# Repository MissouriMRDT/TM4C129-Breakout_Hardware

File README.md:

# TM4C129-Breakout_Hardware
A Hardware breakout for the TM4C129 Microcontroller

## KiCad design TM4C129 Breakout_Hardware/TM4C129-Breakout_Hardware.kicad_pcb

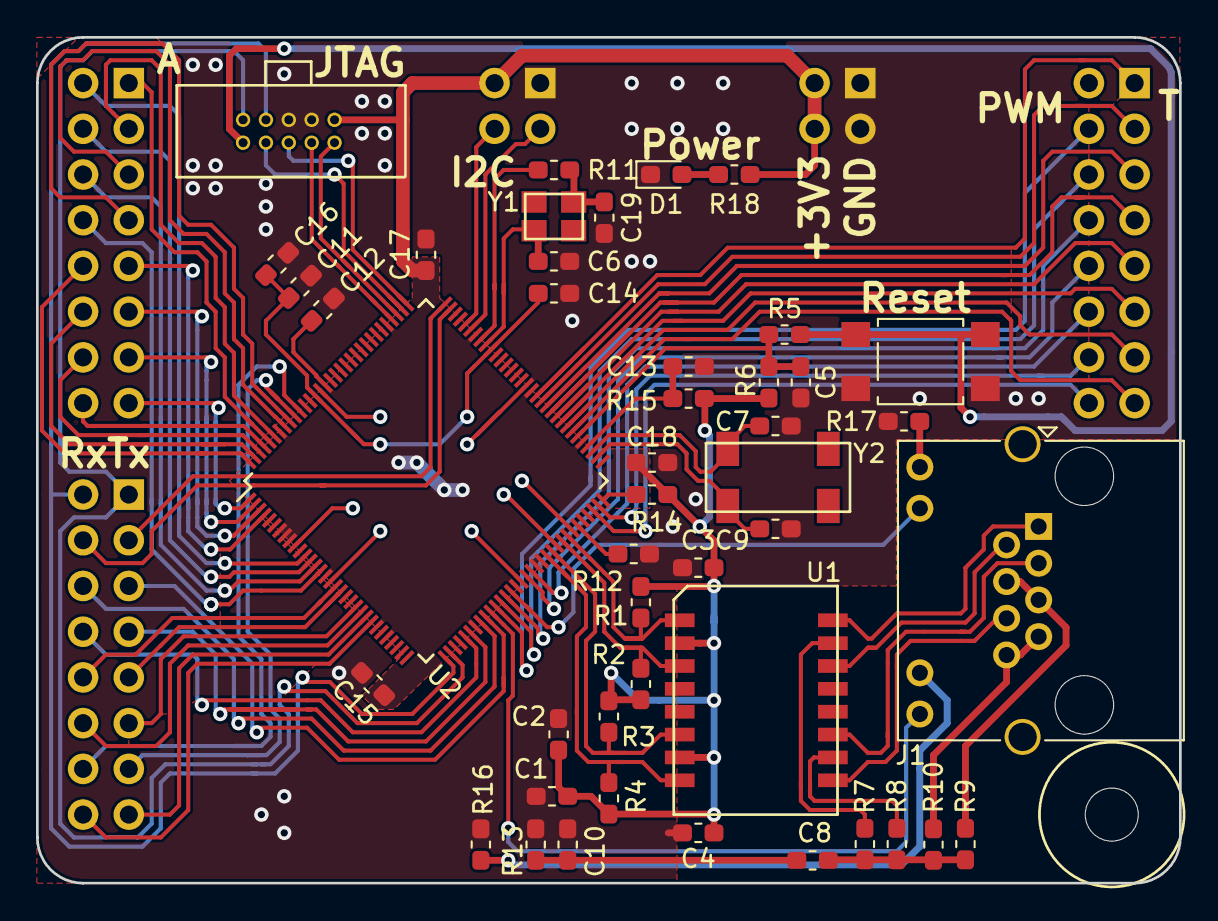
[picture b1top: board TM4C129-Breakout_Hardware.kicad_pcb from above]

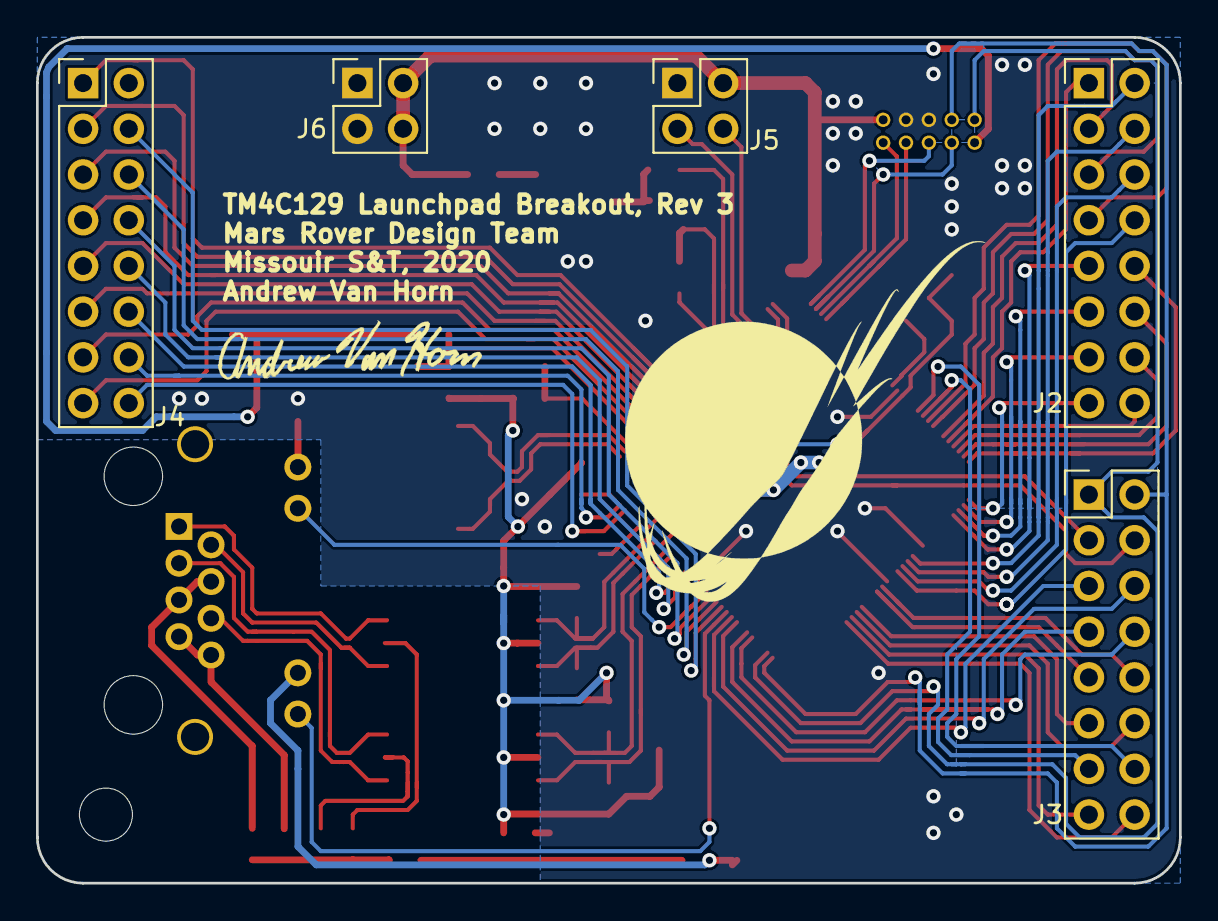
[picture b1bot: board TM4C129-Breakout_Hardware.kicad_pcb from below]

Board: 2 copper layers, 63.5 x 47.0 mm, 50 parts (5 on the bottom side), 85 nets.

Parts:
C1, C2, C3, C4, C5, C13: .1u; C_0603_1608Metric_Pad1.05x0.95mm_HandSolder
C6, C7, C9, C19: 12p; C_0603_1608Metric_Pad1.05x0.95mm_HandSolder
C8: 1000p; C_0603_1608Metric_Pad1.05x0.95mm_HandSolder
C10: 4700p; C_0603_1608Metric_Pad1.05x0.95mm_HandSolder
C11, C12, C15, C17, C18: .1uF; C_0603_1608Metric_Pad1.05x0.95mm_HandSolder
C14: 1uF; C_0603_1608Metric_Pad1.05x0.95mm_HandSolder
C16: 2.2u; C_0603_1608Metric_Pad1.05x0.95mm_HandSolder
Conn1: JTAG_ARM_Connector_10pin; JTAG_ARM_Connector_10_Pin
D1: LED; LED_0603_1608Metric_Pad1.05x0.95mm_HandSolder
J1: RJ45; RJ45_Amphenol_RJHSE538X
J2, J3, J4: Conn_02x08; PinHeader_2x08_P2.54mm_Vertical
J5, J6: Conn_02x02; PinHeader_2x02_P2.54mm_Vertical
R1, R2, R3, R4: 49.9; R_0603_1608Metric_Pad1.05x0.95mm_HandSolder
R5: 100; R_0603_1608Metric_Pad1.05x0.95mm_HandSolder
R6: 10K; R_0603_1608Metric_Pad1.05x0.95mm_HandSolder
R7, R8, R9, R10: 75; R_0603_1608Metric_Pad1.05x0.95mm_HandSolder
R11: 2K; R_0603_1608Metric_Pad1.05x0.95mm_HandSolder
R12: 4.87K; R_0603_1608Metric_Pad1.05x0.95mm_HandSolder
R13, R14: 1M; R_0603_1608Metric_Pad1.05x0.95mm_HandSolder
R15: 51; R_0603_1608Metric_Pad1.05x0.95mm_HandSolder
R16, R17: 330; R_0603_1608Metric_Pad1.05x0.95mm_HandSolder
R18: 500; R_0603_1608Metric_Pad1.05x0.95mm_HandSolder
SW1: Reset; SW_SPST_TL3305A
U1: HX1198FNL
U2: TM4C129ENCPDT; TQFP-128_14x14mm_P0.4mm
Y1: NX3225GA
Y2: Crystal 32K SMD; ABS25

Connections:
+3V3: C1.1, C2.1, C3.1, C4.1, C12.1, C15.1, C17.1, C18.1, Conn1.1, J5.2, J6.2, J6.4, R1.1, R2.1, R3.1, R4.1, R6.2, R14.1, R15.1, R18.1, U1.2, U1.7, U2.7, U2.8, U2.9, U2.16, U2.26, U2.28, U2.39, U2.47, U2.51, U2.52, U2.69, U2.79, U2.90, U2.101, U2.113, U2.122
/OSC0: C6.2, U2.88, Y1.3
/OSC1: R11.1, U2.89
/RBIAS: R12.2, U2.59
/RST_In: C5.2, R5.1, R6.1, U2.70
/VBAT: C13.2, R15.2, U2.68
/Wake: R14.2, U2.64
/XOSC0: C9.2, U2.66, Y2.1
/XOSC1: C7.2, U2.67, Y2.2
A0: J2.2, U2.12
A1: J2.4, U2.13
A2: J2.6, U2.14
A3: J2.8, U2.15
A4: J2.10, U2.128
A5: J2.12, U2.127
A6: J2.14, U2.126
A7: J2.16, U2.125
A8: J2.1, U2.124
A9: J2.3, U2.123
A10: J2.5, U2.121
A11: J2.7, U2.120
A12: J2.9, U2.4
A13: J2.11, U2.3
A14: J2.13, U2.2
A15: J2.15, U2.1
EN0RXI_N: R4.2, U1.8, U2.53
EN0RXI_P: R3.2, U1.6, U2.54
EN0TXO_N: R2.2, U1.3, U2.56
EN0TXO_P: R1.2, U1.1, U2.57
Ethernet_Activity: J1.10, U2.46
Ethernet_Link: J1.12, U2.42
GND: C1.2, C2.2, C3.2, C4.2, C5.1, C6.1, C7.1, C9.1, C10.1, C11.2, C12.2, C13.1, C14.2, C15.2, C16.2, C17.2, C18.2, C19.1, Conn1.3, Conn1.5, D1.1, J5.1, J6.1, J6.3, R12.1, R13.1, R16.2, R17.2, SW1.1, U2.10, U2.17, U2.48, U2.55, U2.58, U2.80, U2.114
unnamed: C8.2, R7.1, R8.1, R9.1, R10.1
unnamed: C8.1, C10.2, R13.2
unnamed: C11.1, C14.1, C16.1, U2.87, U2.115
unnamed: C19.2, R11.2, Y1.1
unnamed: D1.2, R18.2
unnamed: J1.1, U1.16
unnamed: J1.2, U1.14
unnamed: J1.3, U1.11
unnamed: J1.4, J1.5, R9.2
unnamed: J1.6, U1.9
unnamed: J1.7, J1.8, R10.2
unnamed: J1.9, R17.1
unnamed: J1.11, R16.1
unnamed: R7.2, U1.15
unnamed: R8.2, U1.10
PWM1: J4.4, U2.43
PWM2: J4.6, U2.44
PWM3: J4.8, U2.45
PWM4: J4.10, U2.49
PWM5: J4.12, U2.50
PWM6: J4.14, U2.63
PWM7: J4.16, U2.62
RX0: Conn1.7, J3.2, U2.33
RX1: J3.4, U2.95
RX2: J3.6, U2.40
RX3: J3.8, U2.37
RX4: J3.10, U2.18
RX5: J3.12, U2.23
RX6: J3.14, U2.118
RX7: J3.16, U2.25
SCL0: J5.3, U2.91
SDA0: J5.4, U2.92
T2_A: J4.1, U2.78
T2_B: J4.3, U2.77
T3_A: J4.5, U2.76
T3_B: J4.7, U2.75
T4_A: J4.9, U2.74
T4_B: J4.11, U2.73
T5_A: J4.13, U2.72
T5_B: J4.15, U2.71
TCK: Conn1.4, U2.100
TDI: Conn1.8, U2.98
TDO: Conn1.6, U2.97
TMS: Conn1.2, U2.99
TX0: Conn1.9, J3.1, U2.34
TX1: J3.3, U2.96
TX2: J3.5, U2.41
TX3: J3.7, U2.38
TX4: J3.9, U2.19
TX5: J3.11, U2.22
TX6: J3.13, U2.119
TX7: J3.15, U2.24
~RST: Conn1.10, R5.2, SW1.2

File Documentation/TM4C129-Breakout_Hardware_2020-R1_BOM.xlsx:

Id | Designator | Package | Designation |  | Item Name | Part Number |  |  | Vendor | Quantity | Cost Per Item |  | Cost | URL | Comments
1 | J4,J2,J3 | PinHeader_2x08_P2.54mm_Vertical | Conn_02x08 |  | PPTC082LFBN-RC | S7076-ND |  |  | Digikey | 3 | 0.99 |  | 2.9699999999999998 | https://www.digikey.com/product-detail/en/sullins-connector-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
2 | R15 | R_0603_1608Metric_Pad1.05x0.95mm_HandSolder | 51 |  | ERJ-3EKF51R0V | P51.0HCT-ND |  |  | Digikey | 1 | 0.1 |  | 0.1 | https://www.digikey.com/product-detail/en/panasonic-electron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
4 | Y2 | ABS25 | Crystal 32K SMD |  | ABS25-32.000KHZ-T | 535-10242-1-ND |  |  | Digikey | 1 | 1.26 |  | 1.26 | https://www.digikey.com/product-detail/en/abracon-llc/ABS25-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
5 | R1,R2,R3,R4 | R_0603_1608Metric_Pad1.05x0.95mm_HandSolder | 49.9 |  | RC0603FR-0749R9L | 311-49.9HRCT-ND |  |  | Digikey | 4 | 0.1 |  | 0.4 | https://www.digikey.com/product-detail/en/yageo/RC0603FR-074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
6 | U1 | HX1198FNL | HX1198FNL |  | HX1198FNLT | 553-2209-1-ND |  |  | Digikey | 1 | 5.23 |  | 5.23 | https://www.digikey.com/product-detail/en/pulse-electronics-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
7 | R9,R7,R8,R10 | R_0603_1608Metric_Pad1.05x0.95mm_HandSolder | 75 |  | RNCP0603FTD75R0 | RNCP0603FTD75R0CT-ND |  |  | Digikey | 4 | 0.1 |  | 0.4 | https://www.digikey.com/product-detail/en/stackpole-electron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
8 | J1 | RJ45_Amphenol_RJHSE538X | RJ45 |  | 615008137421 | 732-2112-ND |  |  | Digikey | 1 | 2.67 |  | 2.67 | https://www.digikey.com/product-detail/en/w-rth-elektronik/6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
9 | R16,R17 | R_0603_1608Metric_Pad1.05x0.95mm_HandSolder | 330 |  | ERJ-3EKF3300V | P330HCT-ND |  |  | Digikey | 2 | 0.1 |  | 0.2 | https://www.digikey.com/product-detail/en/panasonic-electron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
10 | R13,R14 | R_0603_1608Metric_Pad1.05x0.95mm_HandSolder | 1M |  | RC0603FR-071ML | 311-1.00MHRCT-ND |  |  | Digikey | 2 | 0.1 |  | 0.2 | https://www.digikey.com/product-detail/en/yageo/RC0603FR-071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
11 | C8 | C_0603_1608Metric_Pad1.05x0.95mm_HandSolder | 1000p |  | C0603C102K4RACTU | 399-7835-1-ND |  |  | Digikey | 1 | 0.11 |  | 0.11 | https://www.digikey.com/product-detail/en/kemet/C0603C102K4R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
12 | C10 | C_0603_1608Metric_Pad1.05x0.95mm_HandSolder | 4700p |  | C0603C472K4RACTU | 399-9091-1-ND |  |  | Digikey | 1 | 0.1 |  | 0.1 | https://www.digikey.com/product-detail/en/kemet/C0603C472K4R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
13 | U2 | TQFP-128_14x14mm_P0.4mm | TM4C129ENCPDT |  | TM4C1294NCPDTI3R | 296-46223-1-ND |  |  | Digikey | 1 | 15.36 |  | 15.36 | https://www.digikey.com/product-detail/en/texas-instruments/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
14 | Conn1 | JTAG_ARM_Connector_10_Pin | JTAG_ARM_Connector_10pin |  | 3220-10-0100-00 | 1175-1627-ND |  |  | Digikey | 1 | 0.57999999999999996 |  | 0.57999999999999996 | https://www.digikey.com/product-detail/en/cnc-tech/3220-10-0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
15 | Y1 | NX3225GA | NX3225GA |  | NX3225GA-26MHZ-TI | 644-1160-1-ND |  |  | Digikey | 1 | 0.69 |  | 0.69 | https://www.digikey.com/product-detail/en/ndk-america-inc/NX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
16 | C6,C7,C9 | C_0603_1608Metric_Pad1.05x0.95mm_HandSolder | 12p |  | VJ0603A120FXJPW1BC | 720-1654-1-ND |  |  | Digikey | 3 | 0.26 |  | 0.78 | https://www.digikey.com/product-detail/en/vishay-vitramon/VJ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
17 | C13,C2,C1,C3,C4,C5,C11,C12,C14,C15,C17,C18 | C_0603_1608Metric_Pad1.05x0.95mm_HandSolder | .1uF |  | CL10B104KO8NNNC | 1276-1005-1-ND |  |  | Digikey | 11 | 0.1 |  | 1.1000000000000001 | https://www.digikey.com/product-detail/en/samsung-electro-me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
18 | C16 | C_0603_1608Metric_Pad1.05x0.95mm_HandSolder | 2.2u |  | C0603C225K4PACTU | 399-7886-1-ND |  |  | Digikey | 1 | 0.14000000000000001 |  | 0.14000000000000001 | https://www.digikey.com/product-detail/en/kemet/C0603C225K4P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
19 | J5,J6 | PinHeader_2x02_P2.54mm_Vertical | Conn_02x02 |  | PPPC022LFBN-RC | S7105-ND |  |  | Digikey | 2 | 0.57999999999999996 |  | 1.1599999999999999 | https://www.digikey.com/product-detail/en/sullins-connector-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
20 | R5 | R_0603_1608Metric_Pad1.05x0.95mm_HandSolder | 100 |  | RC0603FR-07100RL | 311-100HRCT-ND |  |  | Digikey | 1 | 0.1 |  | 0.1 | https://www.digikey.com/product-detail/en/yageo/RC0603FR-071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
21 | R6 | R_0603_1608Metric_Pad1.05x0.95mm_HandSolder | 10K |  | ESR03EZPF1002 | RHM10KADCT-ND |  |  | Digikey | 1 | 0.13 |  | 0.13 | https://www.digikey.com/product-detail/en/rohm-semiconductor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
22 | R11 | R_0603_1608Metric_Pad1.05x0.95mm_HandSolder | 2K |  | RC0603FR-072KL | 311-2.00KHRCT-ND |  |  | Digikey | 1 | 0.1 |  | 0.1 | https://www.digikey.com/product-detail/en/yageo/RC0603FR-072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
23 | R12 | R_0603_1608Metric_Pad1.05x0.95mm_HandSolder | 4.87K |  | RMCF0603FT4K87 | RMCF0603FT4K87CT-ND |  |  | Digikey | 1 | 0.1 |  | 0.1 | https://www.digikey.com/product-detail/en/stackpole-electron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
24 | SW1 | SW_SPST_TL3305A | SW_Push |  | TL3305AF160QG | EG5350CT-ND |  |  | Digikey | 1 | 0.2 |  | 0.2 | https://www.digikey.com/product-detail/en/e-switch/TL3305AF1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
25 |  | C_0603_1608Metric_Pad1.05x0.95mm_HandSolder | 1uF |  |  |  |  |  | Digikey | 1

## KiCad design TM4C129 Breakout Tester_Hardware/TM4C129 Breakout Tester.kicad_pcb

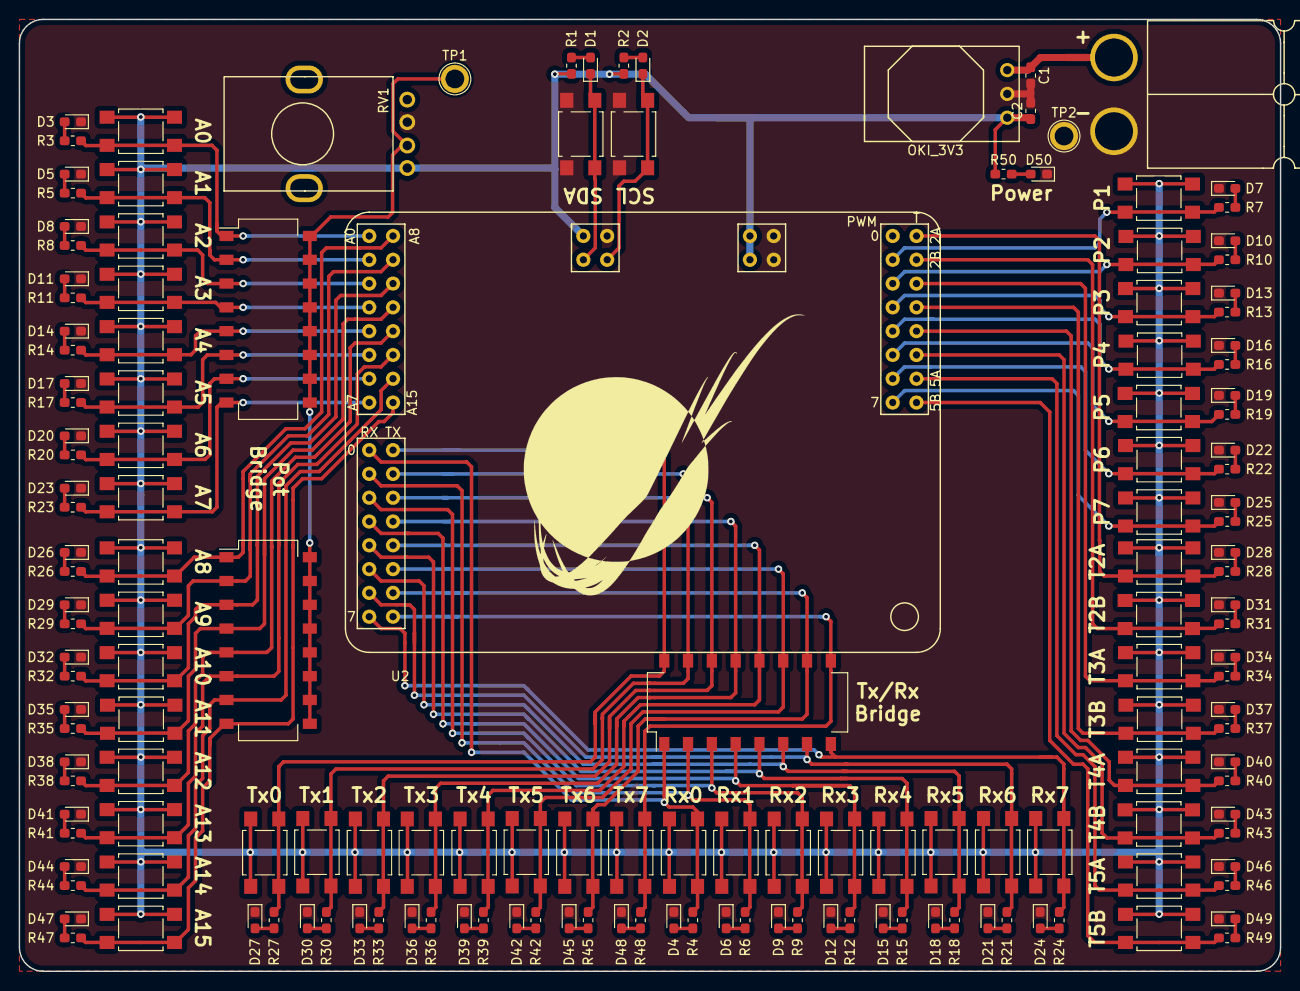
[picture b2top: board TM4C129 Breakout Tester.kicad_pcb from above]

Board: 2 copper layers, 134.6 x 101.6 mm, 160 parts (0 on the bottom side), 103 nets.

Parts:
C1, C2: 10u; C_0603_1608Metric_Pad1.05x0.95mm_HandSolder
Conn1: AndersonPP; Anderson_2_Horizontal_Side_by_Side
D1, D2, D3, D4, D5, D6, D7, D8, D9, D10, D11, D12, D13, D14, D15, D16, D17, D18, D19, D20, D21, D22, D23, D24, D25, D26, D27, D28, D29, D30, D31, D32, D33, D34, D35, D36, D37, D38, D39, D40, D41, D42, D43, D44, D45, D46, D47, D48, D49, D50: LED_Small; LED_0603_1608Metric_Pad1.05x0.95mm_HandSolder
R1, R2, R3, R4, R5, R6, R7, R8, R9, R10, R11, R12, R13, R14, R15, R16, R17, R18, R19, R20, R21, R22, R23, R24, R25, R26, R27, R28, R29, R30, R31, R32, R33, R34, R35, R36, R37, R38, R39, R40, R41, R42, R43, R44, R45, R46, R47, R48, R49, R50: 500; R_0603_1608Metric_Pad1.05x0.95mm_HandSolder
RV1: R_POT; P110KH
SW1, SW2, SW3, SW4, SW5, SW6, SW7, SW8, SW9, SW10, SW11, SW12, SW13, SW14, SW15, SW16, SW17, SW18, SW19, SW20, SW21, SW22, SW23, SW24, SW25, SW26, SW27, SW28, SW29, SW30, SW31, SW32, SW33, SW34, SW35, SW36, SW37, SW38, SW39, SW40, SW41, SW42, SW43, SW44, SW45, SW46, SW47, SW48, SW49: SW_Push; SW_SPST_TL3305A
SW50, SW51, SW52: SW_DIP_x08; SW_DIP_SPSTx08_Slide_Omron_A6S-810x_W8.9mm_P2.54mm
TP1, TP2: TestPoint; TestPoint_Plated_Hole_D2.0mm
U1: OKI_3V3; OKI_Horizontal
U2: TM4C129Breakout; TM4C129Breakout_THT

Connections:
+3V3: C2.1, R1.1, R2.1, R50.1, RV1.1, SW1.1, SW2.1, SW3.1, SW4.1, SW5.1, SW6.1, SW7.1, SW8.1, SW9.1, SW10.1, SW11.1, SW12.1, SW13.1, SW14.1, SW15.1, SW16.1, SW17.1, SW18.1, SW19.1, SW20.1, SW21.1, SW22.1, SW23.1, SW24.1, SW25.1, SW26.1, SW27.1, SW28.1, SW29.1, SW30.1, SW31.1, SW32.1, SW33.1, SW34.1, SW35.1, SW36.1, SW37.1, SW38.1, SW39.1, SW40.1, SW41.1, SW42.1, SW43.1, SW44.1, SW45.1, SW46.1, SW47.1, U1.3, U2.+3V3
A0: R3.1, SW1.2, SW50.1, U2.PE3
A1: R5.1, SW2.2, SW50.2, U2.PE2
A2: R8.1, SW3.2, SW50.3, U2.PE1
A3: R11.1, SW4.2, SW50.4, U2.PE0
A4: R14.1, SW5.2, SW50.5, U2.PD7
A5: R17.1, SW6.2, SW50.6, U2.PD6
A6: R20.1, SW7.2, SW50.7, U2.PD5
A7: R23.1, SW8.2, SW50.8, U2.PD4
A8: R26.1, SW9.2, SW51.1, U2.PE5
A9: R29.1, SW10.2, SW51.2, U2.PE4
A10: R32.1, SW11.2, SW51.3, U2.PB4
A11: R35.1, SW12.2, SW51.4, U2.PB5
A12: R38.1, SW13.2, SW51.5, U2.PD3
A13: R41.1, SW14.2, SW51.6, U2.PD2
A14: R44.1, SW15.2, SW51.7, U2.PD1
A15: R47.1, SW16.2, SW51.8, U2.PD0
GND: C1.2, C2.2, Conn1.1, D3.1, D4.1, D5.1, D6.1, D7.1, D8.1, D9.1, D10.1, D11.1, D12.1, D13.1, D14.1, D15.1, D16.1, D17.1, D18.1, D19.1, D20.1, D21.1, D22.1, D23.1, D24.1, D25.1, D26.1, D27.1, D28.1, D29.1, D30.1, D31.1, D32.1, D33.1, D34.1, D35.1, D36.1, D37.1, D38.1, D39.1, D40.1, D41.1, D42.1, D43.1, D44.1, D45.1, D46.1, D47.1, D48.1, D49.1, D50.1, RV1.3, SW48.2, SW49.2, TP2.1, U1.2, U2.GND
unnamed: C1.1, Conn1.2, U1.1
unnamed: D1.2, R1.2
unnamed: D2.2, R2.2
unnamed: D3.2, R3.2
unnamed: D4.2, R4.2
unnamed: D5.2, R5.2
unnamed: D6.2, R6.2
unnamed: D7.2, R7.2
unnamed: D8.2, R8.2
unnamed: D9.2, R9.2
unnamed: D10.2, R10.2
unnamed: D11.2, R11.2
unnamed: D12.2, R12.2
unnamed: D13.2, R13.2
unnamed: D14.2, R14.2
unnamed: D15.2, R15.2
unnamed: D16.2, R16.2
unnamed: D17.2, R17.2
unnamed: D18.2, R18.2
unnamed: D19.2, R19.2
unnamed: D20.2, R20.2
unnamed: D21.2, R21.2
unnamed: D22.2, R22.2
unnamed: D23.2, R23.2
unnamed: D24.2, R24.2
unnamed: D25.2, R25.2
unnamed: D26.2, R26.2
unnamed: D27.2, R27.2
unnamed: D28.2, R28.2
unnamed: D29.2, R29.2
unnamed: D30.2, R30.2
unnamed: D31.2, R31.2
unnamed: D32.2, R32.2
unnamed: D33.2, R33.2
unnamed: D34.2, R34.2
unnamed: D35.2, R35.2
unnamed: D36.2, R36.2
unnamed: D37.2, R37.2
unnamed: D38.2, R38.2
unnamed: D39.2, R39.2
unnamed: D40.2, R40.2
unnamed: D41.2, R41.2
unnamed: D42.2, R42.2
unnamed: D43.2, R43.2
unnamed: D44.2, R44.2
unnamed: D45.2, R45.2
unnamed: D46.2, R46.2
unnamed: D47.2, R47.2
unnamed: D48.2, R48.2
unnamed: D49.2, R49.2
unnamed: D50.2, R50.2
unnamed: RV1.2, SW50.9, SW50.10, SW50.11, SW50.12, SW50.13, SW50.14, SW50.15, SW50.16, SW51.9, SW51.10, SW51.11, SW51.12, SW51.13, SW51.14, SW51.15, SW51.16, TP1.1
PWM1: R7.1, SW33.2, U2.PF1
PWM2: R10.1, SW34.2, U2.PF2
PWM3: R13.1, SW35.2, U2.PF3
PWM4: R16.1, SW36.2, U2.PG0
PWM5: R19.1, SW37.2, U2.PG1
PWM6: R22.1, SW38.2, U2.PK4
PWM7: R25.1, SW39.2, U2.PK5
Rx0: R4.1, SW17.2, SW52.1, U2.PA0
Rx1: R6.1, SW18.2, SW52.2, U2.PB0
Rx2: R9.1, SW19.2, SW52.3, U2.PA6
Rx3: R12.1, SW20.2, SW52.4, U2.PA4
Rx4: R15.1, SW21.2, SW52.5, U2.PK0
Rx5: R18.1, SW22.2, SW52.6, U2.PC6
Rx6: R21.1, SW23.2, SW52.7, U2.PP0
Rx7: R24.1, SW24.2, SW52.8, U2.PC4
SCL0: D2.1, SW48.1, U2.PB2
SDA0: D1.1, SW49.1, U2.PB3
T2A: R28.1, SW40.2, U2.PM0
T2B: R31.1, SW41.2, U2.PM1
T3A: R34.1, SW42.2, U2.PM2
T3B: R37.1, SW43.2, U2.PM3
T4A: R40.1, SW44.2, U2.PM4
T4B: R43.1, SW45.2, U2.PM5
T5A: R46.1, SW46.2, U2.PM6
T5B: R49.1, SW47.2, U2.PM7
Tx0: R27.1, SW25.2, SW52.16, U2.PA1
Tx1: R30.1, SW26.2, SW52.15, U2.PB1
Tx2: R33.1, SW27.2, SW52.14, U2.PA7
Tx3: R36.1, SW28.2, SW52.13, U2.PA5
Tx4: R39.1, SW29.2, SW52.12, U2.PK1
Tx5: R42.1, SW30.2, SW52.11, U2.PC7
Tx6: R45.1, SW31.2, SW52.10, U2.PP1
Tx7: R48.1, SW32.2, SW52.9, U2.PC5

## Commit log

2019-11-09 added ethernet circuitry
2019-11-10 Assigned footprints
2019-11-16 started high-level layout
2019-11-17 Ran TIVA Traces
2019-11-17 Cleaned up Schematic
2019-11-17 Wired left half traces
2019-11-17 did ethernet circuitry
2019-11-18 Finished layout and critical traces
2019-11-25 finished layout
2019-12-01 Moved hardware files out of redundant foler
2019-12-01 Completed BOM
2019-12-03 fixed headers to go down
2019-12-13 fixed changes before PRR
2019-12-13 Minor Aesthetic changes
2019-12-13 Final changes before PRR
2019-12-13 Added bom
2019-12-14 Update sym-lib-table
2019-12-14 Added Gerbs
2019-12-14 Revert "Merge branch 'master' of https://github.com/MissouriMRDT/TM4C129-Breakout_Hardware"
    This reverts commit e6cd920ed13198a4f7d11fd6171e0ba52050bff9, reversing
    changes made to e15dd7d36717f2d892901729c8f3941fb424f385.
2019-12-14 Revert "Revert "Merge branch 'master' of https://github.com/MissouriMRDT/TM4C129-Breakout_Hardware""
    This reverts commit 4686fe645caf3e9fbf8c00f0c0ea95986b0ea6b8.
2019-12-14 changed naming in schematic
2019-12-14 Moved gerbs to documentation
2020-01-10 made tester board
2020-01-11 Touchpus and Silkscreen
2020-01-11 Updated breakout footprint
2020-01-11 updated TM4c layout
2020-01-31 Fixed ethernet wiring to conform to best practices.
2020-03-04 Created Rev3 Gerbs
